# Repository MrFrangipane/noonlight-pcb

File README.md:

# Noon Light - PCB

Electronics for a RaspberryPico(W) based, LED Strip driving, DMX fixture

## Schematics

### PCB

| 3D front | 3D back | PCB |
|---|---|---|
|  |  |  |

## Links

-  https://electricfiredesign.com/2021/03/12/logic-level-shifters-for-driving-led-strips/
- https://www.theatrelightingworkshops.com/dmx-to-analog-conversion/

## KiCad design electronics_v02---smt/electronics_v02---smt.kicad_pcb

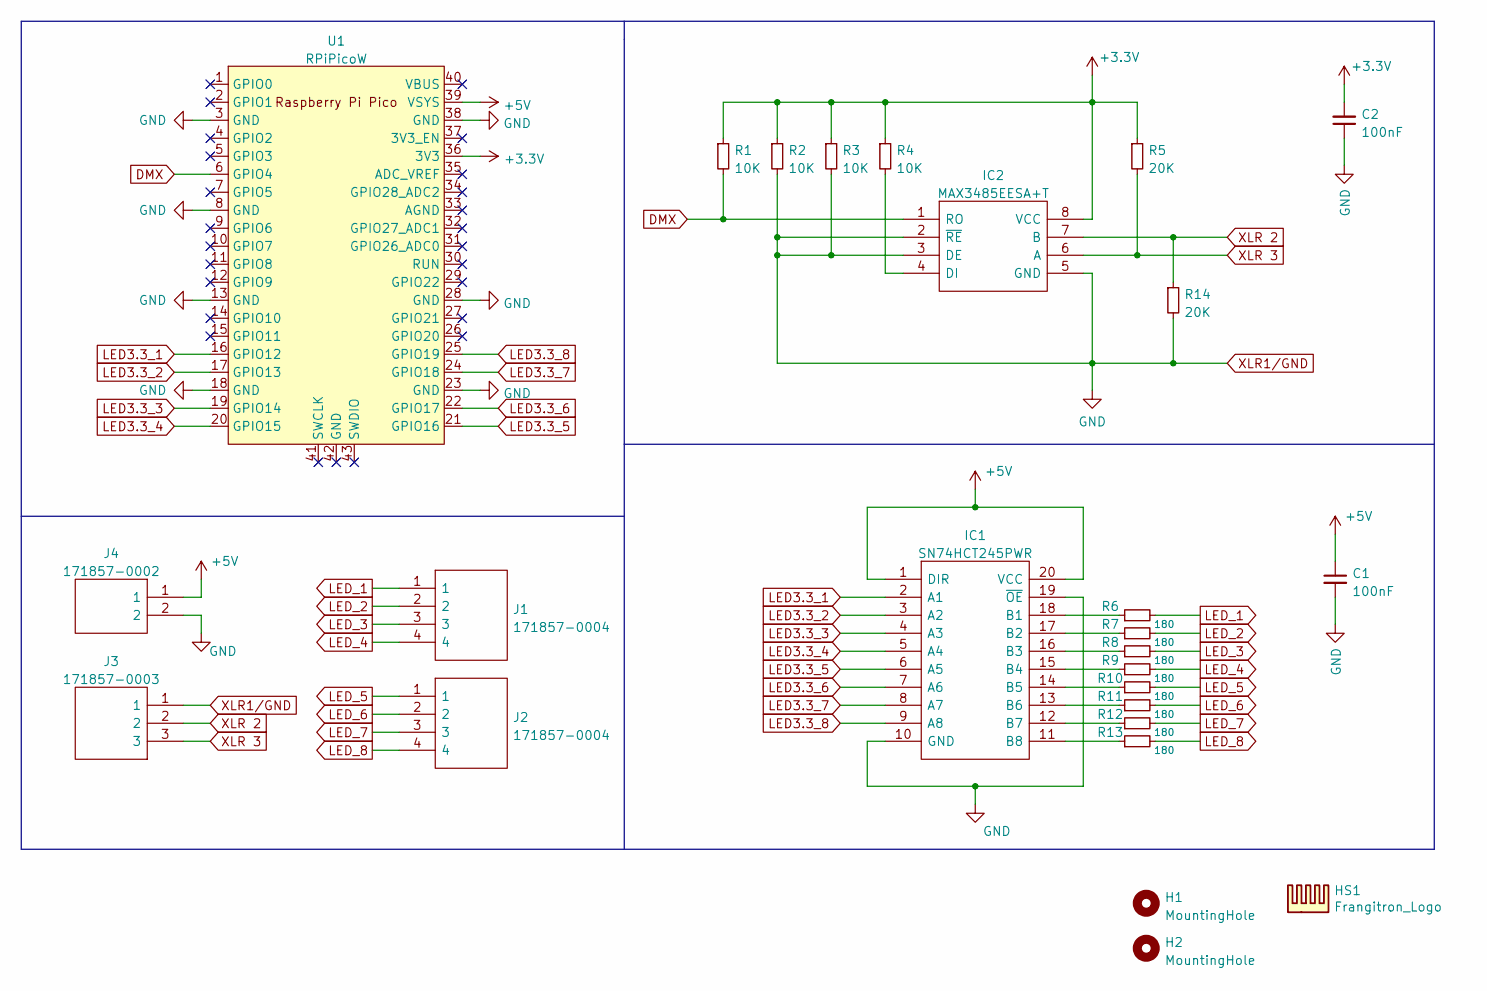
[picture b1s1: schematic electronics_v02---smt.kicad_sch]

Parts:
C1, C2: 100nF; C_0402_1005Metric; LCSC Part Number C1525
H1, H2: MountingHole; MountingHole_2.5mm
HS1: Frangitron_Logo; frangitron_logo_16mm
IC1: SN74HCT245PWR; SOP65P640X120-20N; Mouser Part Number 595-SN74HCT245PWR
IC2: MAX3485EESA+T; SOIC127P600X175-8N; Mouser Part Number 700-MAX3485EESAT
J1, J2: 171857-0004; HDRRA4W64P0X254_1X4_1001X318X635P; Mouser Part Number 538-171857-0004
J3: 171857-0003; Mouser Part Number 538-171857-0003
J4: 171857-0002; Mouser Part Number 538-171857-0002
R1, R2, R3, R4: 10K; R_0603_1608Metric; LCSC Part Number C15401
R5, R14: 20K; R_0805_2012Metric; LCSC Part Number C4328
R6, R7, R8, R9, R10, R11, R12, R13: 180; R_0805_2012Metric; LCSC Part Number C25270
U1: RPiPicoW; RaspberryPicoW

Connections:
+3.3V: C2.2, IC2.8 (VCC), R1.1, R2.1, R3.1, R4.1, R5.1, U1.36 (3V3)
+5V: C1.1, IC1.1 (DIR), IC1.20 (VCC), J4.1, U1.39 (VSYS)
DMX: IC2.1 (RO), R1.2, U1.6 (GPIO4)
LED3.3_1: IC1.2 (A1), U1.16 (GPIO12)
LED3.3_2: IC1.3 (A2), U1.17 (GPIO13)
LED3.3_3: IC1.4 (A3), U1.19 (GPIO14)
LED3.3_4: IC1.5 (A4), U1.20 (GPIO15)
LED3.3_5: IC1.6 (A5), U1.21 (GPIO16)
LED3.3_6: IC1.7 (A6), U1.22 (GPIO17)
LED3.3_7: IC1.8 (A7), U1.24 (GPIO18)
LED3.3_8: IC1.9 (A8), U1.25 (GPIO19)
LED_1: J1.1, R6.2
LED_2: J1.2, R7.2
LED_3: J1.3, R8.2
LED_4: J1.4, R9.2
LED_5: J2.1, R10.2
LED_6: J2.2, R11.2
LED_7: J2.3, R12.2
LED_8: J2.4, R13.2
unnamed: IC1.11 (B8), R13.1
unnamed: IC1.12 (B7), R12.1
unnamed: IC1.13 (B6), R11.1
unnamed: IC1.14 (B5), R10.1
unnamed: IC1.15 (B4), R9.1
unnamed: IC1.16 (B3), R8.1
unnamed: IC1.17 (B2), R7.1
unnamed: IC1.18 (B1), R6.1
unnamed: IC2.4 (DI), R4.2
XLR1/GND: C1.2, C2.1, IC1.10 (GND), IC1.19 (~OE), IC2.2 (~RE), IC2.3 (DE), IC2.5 (GND), J3.1, J4.2, R2.2, R3.2, R14.2, U1.3 (GND), U1.8 (GND), U1.13 (GND), U1.18 (GND), U1.23 (GND), U1.28 (GND), U1.38 (GND)
XLR 2: IC2.7 (B), J3.2, R14.1
XLR 3: IC2.6 (A), J3.3, R5.2

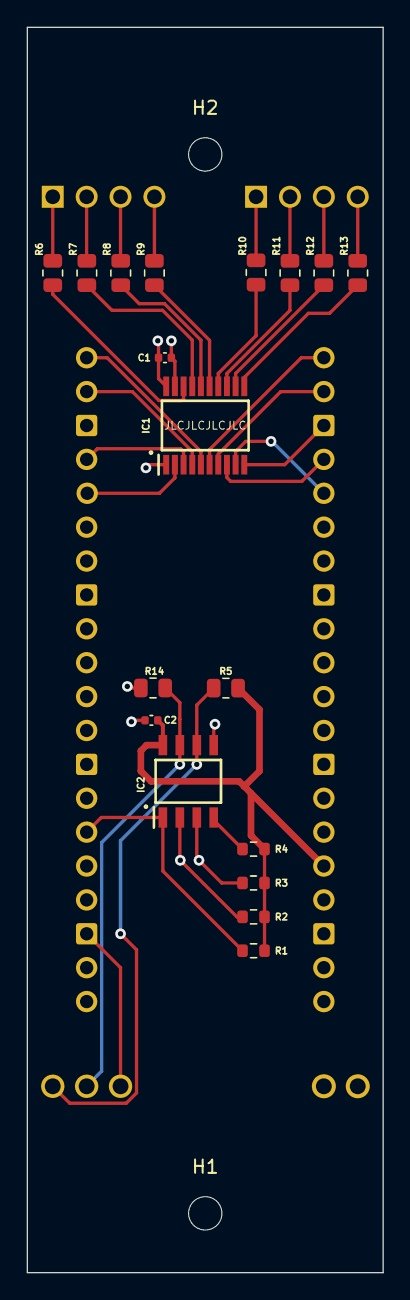
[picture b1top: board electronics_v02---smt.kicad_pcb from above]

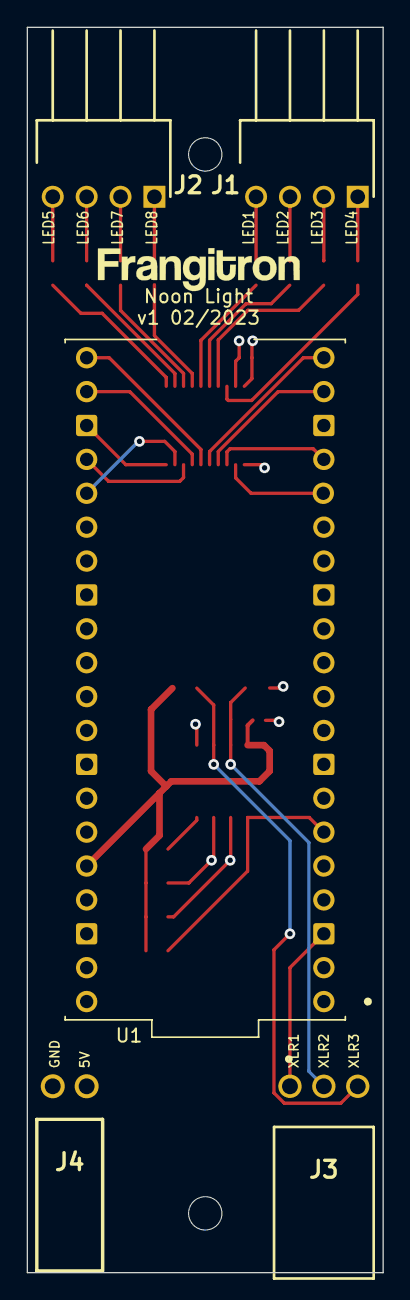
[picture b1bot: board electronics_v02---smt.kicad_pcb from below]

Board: 4 copper layers, 26.7 x 93.3 mm, 26 parts (6 on the bottom side), 31 nets.

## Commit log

2023-02-26 manual file copy
2023-02-26 Fix 3D images
